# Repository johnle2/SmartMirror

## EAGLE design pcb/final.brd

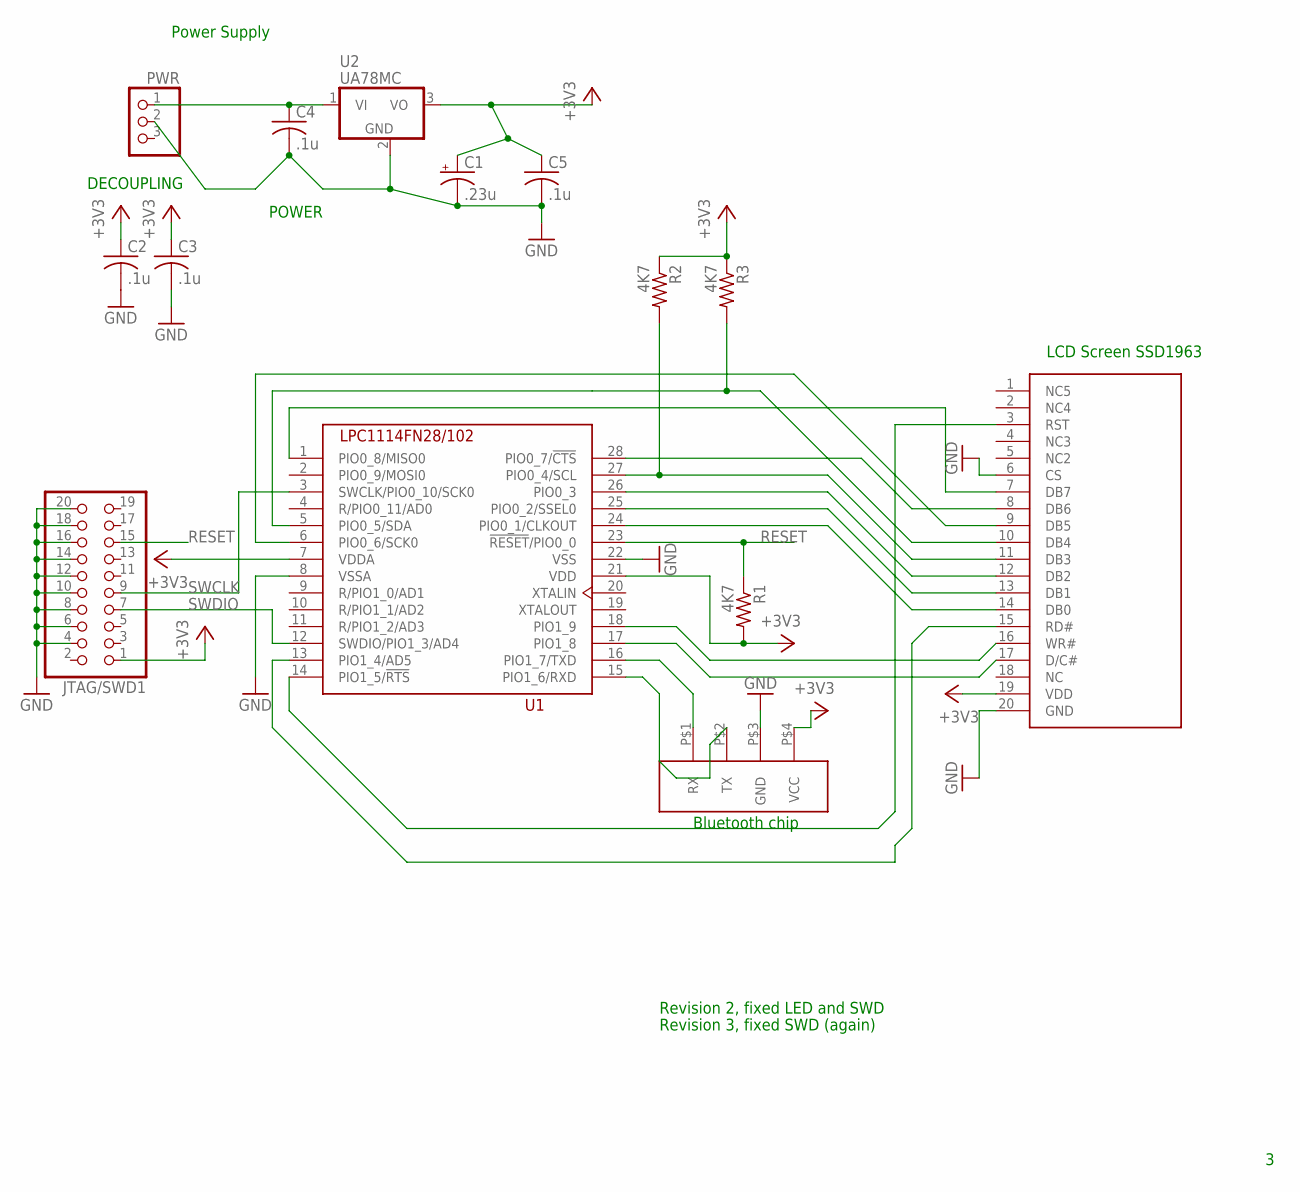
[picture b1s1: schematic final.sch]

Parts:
C1: .23u; E3,5-8
C2, C3, C4, C5: .1u; C050-024X044
JTAG/SWD1: PINHD-2X10; 2X10
PWR: PINHD-1X3; 1X03
R1, R2, R3: 4K7; 0207/10
U1: LPC1114FN28/102; DIL28-6
U2: UA78MC; TO220V
U$1: BLUETOOTH
U$2: LCD_TOUCH; NHD-7.0-800480WF

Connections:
+3V3: C1.+, C2.1, C3.1, C5.1, JTAG/SWD1.1, R1.2, R2.1, R3.1, U1.7 (VDDA), U1.21 (VDD), U2.3 (VO), U$1.P$4 (VCC), U$2.19 (VDD)
GND: C1.-, C2.2, C3.2, C4.2, C5.2, JTAG/SWD1.4, JTAG/SWD1.6, JTAG/SWD1.8, JTAG/SWD1.10, JTAG/SWD1.12, JTAG/SWD1.14, JTAG/SWD1.16, JTAG/SWD1.18, JTAG/SWD1.20, PWR.2, U1.8 (VSSA), U1.22 (VSS), U2.2 (GND), U$1.P$3 (GND), U$2.6 (CS), U$2.20 (GND)
unnamed: C4.1, PWR.1, U2.1 (VI)
unnamed: U1.6 (PIO0_6/SCK0), U$2.9 (DB5)
unnamed: U1.1 (PIO0_8/MISO0), U$2.7 (DB7)
unnamed: U1.16 (PIO1_7/TXD), U$1.P$1 (RX)
unnamed: U1.13 (PIO1_4/AD5), U$2.15 (RD#)
unnamed: U1.15 (PIO1_6/RXD), U$1.P$2 (TX)
unnamed: R3.2, U$2.10 (DB4)
unnamed: R2.2, U1.27 (PIO0_4/SCL), U$2.11 (DB3)
unnamed: U1.26 (PIO0_3), U$2.12 (DB2)
unnamed: U1.25 (PIO0_2/SSEL0), U$2.13 (DB1)
unnamed: U1.24 (PIO0_1/CLKOUT), U$2.14 (DB0)
unnamed: U1.28 (PIO0_7/!CTS), U$2.8 (DB6)
unnamed: U1.14 (PIO1_5/!RTS), U$2.3 (RST)
unnamed: U1.17 (PIO1_8), U$2.17 (D/C#)
unnamed: U1.18 (PIO1_9), U$2.16 (WR#)
RESET: JTAG/SWD1.15, R1.1, U1.23 (!RESET!/PIO0_0)
SWCLK: JTAG/SWD1.9, U1.3 (SWCLK/PIO0_10/SCK0)
SWDIO: JTAG/SWD1.7, U1.12 (SWDIO/PIO1_3/AD4)

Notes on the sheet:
POWER
DECOUPLING
Revision 2, fixed LED and SWD
Revision 3, fixed SWD (again)
Power Supply
LCD Screen SSD1963
Bluetooth chip

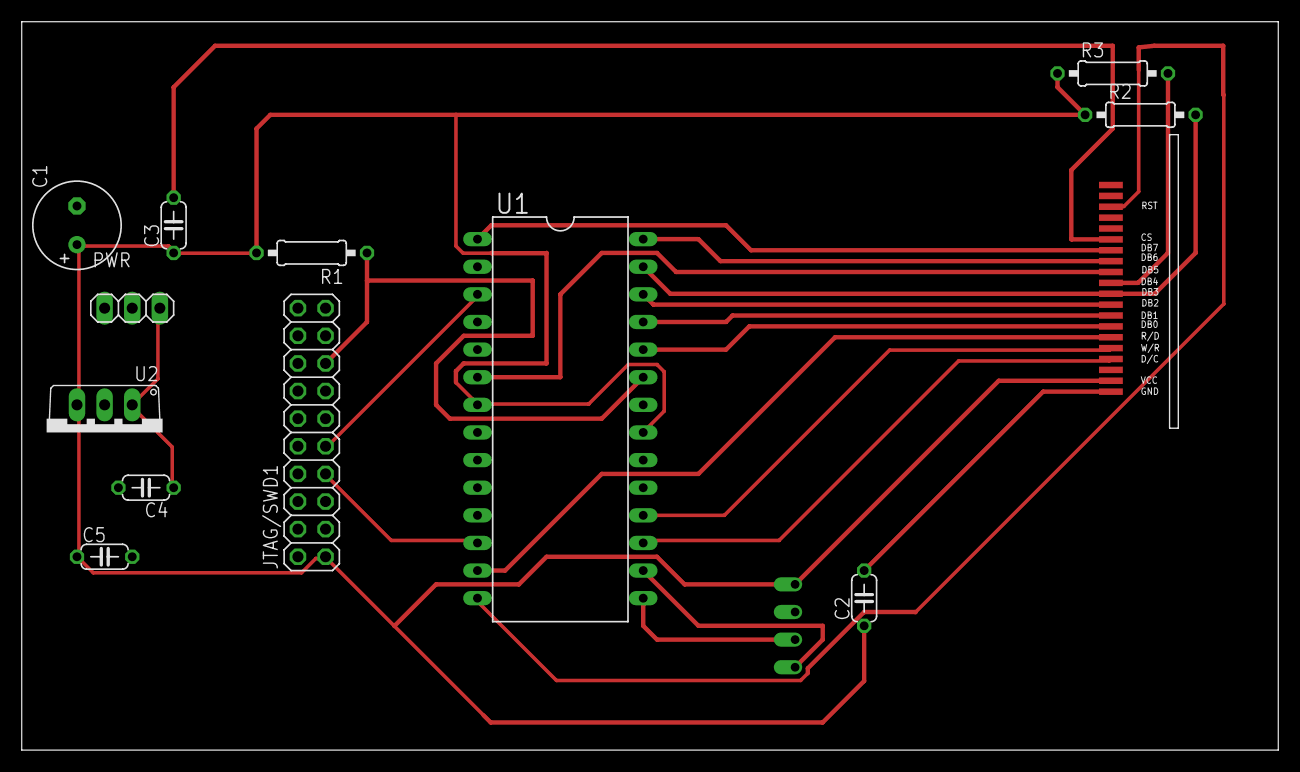
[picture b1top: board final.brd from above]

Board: 2 copper layers, 115.6 x 67.0 mm, 14 parts (1 on the bottom side), 20 nets.

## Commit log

2017-06-13 Import project
